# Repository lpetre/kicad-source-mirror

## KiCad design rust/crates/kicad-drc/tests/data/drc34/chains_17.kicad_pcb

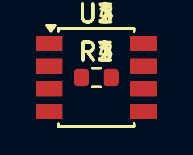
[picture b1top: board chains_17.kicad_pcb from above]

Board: 2 copper layers, 8 parts (0 on the bottom side), 6 nets.

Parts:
R1, R2, R3, R4: R; R_0603_1608Metric
U1, U2, U3, U4: TL071; SSOP-8_3.95x5.21x3.27mm_P1.27mm

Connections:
unnamed: R1.1, U1.6
unnamed: R1.2, R2.1
unnamed: R2.2, U2.6
unnamed: R3.1, U3.6
unnamed: R3.2, R4.1
unnamed: R4.2, U4.6

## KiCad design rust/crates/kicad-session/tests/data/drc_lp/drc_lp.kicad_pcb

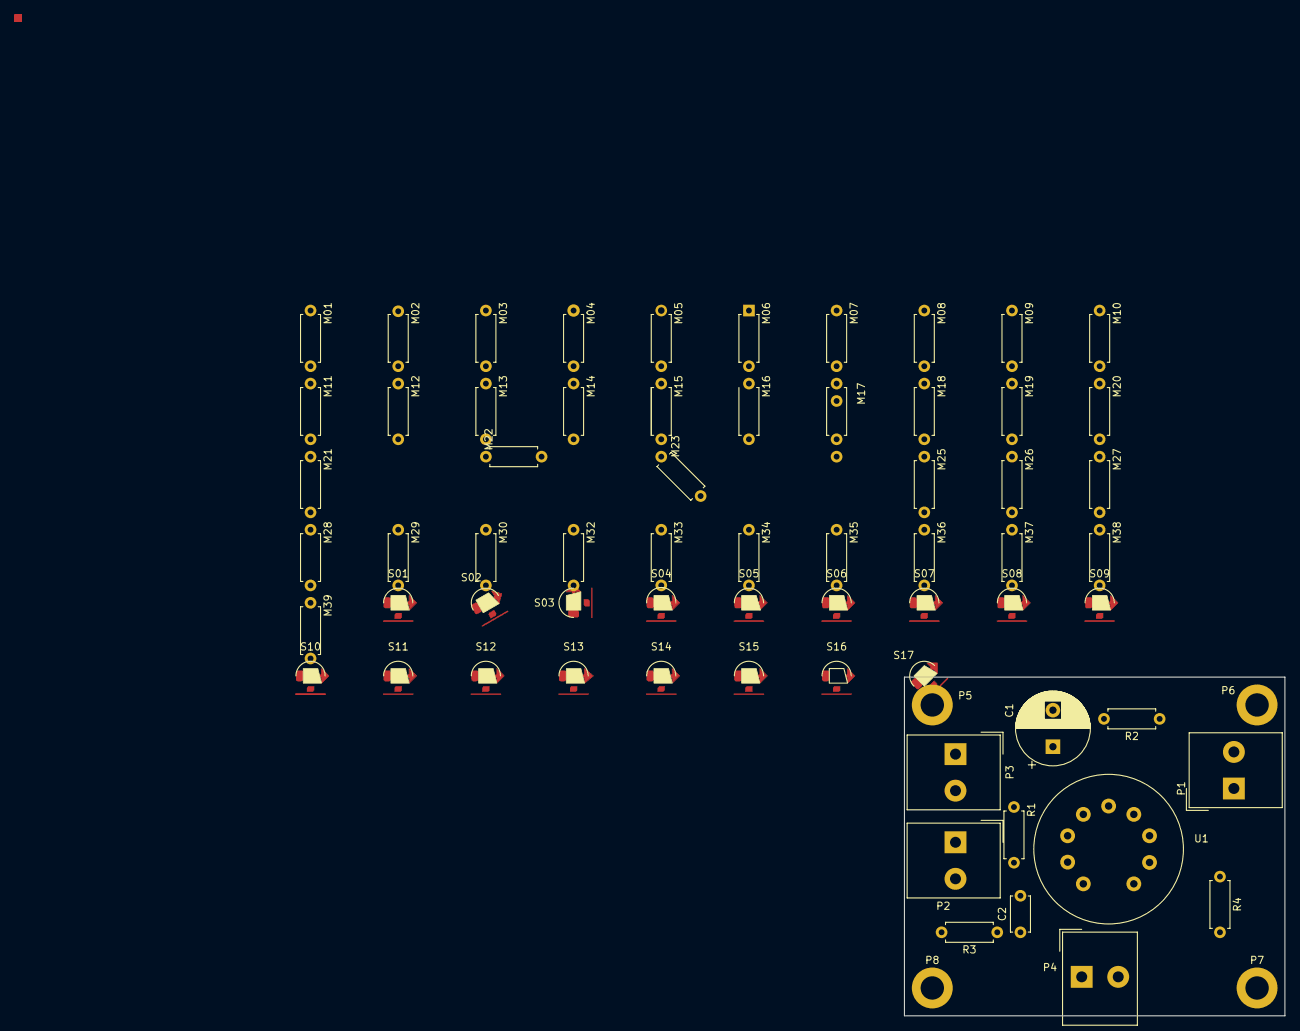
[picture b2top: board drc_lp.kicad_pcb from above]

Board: 2 copper layers, 52.1 x 46.4 mm, 76 parts (1 on the bottom side), 9 nets, no tracks yet.

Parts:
C1: 10uF; CP_Radial_D10.0mm_P5.00mm
C2: 680nF; C_Disc_D4.7mm_W2.5mm_P5.00mm
M01, M02, M03, M04, M05, M06, M07, M08, M09, M10, M11, M12, M13, M14, M15, M16, M17, M18, M19, M20, M21, M22, M23, M24, M25, M26, M27, M28, M29, M32, M33, M34, M35, M36, M37, M38, M39: 1.5K; R_Axial_DIN0207_L6.3mm_D2.5mm_P7.62mm_Horizontal
M30: 1.5K; NoSuchFootprint
P1: IN; Altech_AK300_1x02_P5.00mm_45-Degree
P2: OUT; Altech_AK300_1x02_P5.00mm_45-Degree
P3: POWER; Altech_AK300_1x02_P5.00mm_45-Degree
P4: CONN_2; Altech_AK300_1x02_P5.00mm_45-Degree
P5, P6, P7, P8: MOUNTING_HOLE; MountingHole_3.2mm_M3_DIN965_Pad
R1, R2: 1.5K; R_Axial_DIN0207_L6.3mm_D2.5mm_P7.62mm_Horizontal
R3: 100K; R_Axial_DIN0207_L6.3mm_D2.5mm_P7.62mm_Horizontal
R4: 47K; R_Axial_DIN0207_L6.3mm_D2.5mm_P7.62mm_Horizontal
S01, S02, S03, S04, S05, S06, S07, S08, S09, S10, S11, S12, S13, S14, S15, S16, S17: Shapes
U1: ECC83; Valve_ECC-83-1
Z01, Z02, Z03, Z04, Z05, Z06: ZoneFp

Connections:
GND: C1.2, P1.1, P2.2 (PM), P3.2 (PM), R2.2, R3.2, R4.2
unnamed: P1.2 (PM), R4.1, U1.2 (G)
unnamed: C2.1, P2.1, R3.1
unnamed: C1.1, P3.1, U1.6 (A)
unnamed: P4.1, U1.9 (F2)
unnamed: P4.2 (PM), U1.4 (F1), U1.5 (F1)
unnamed: R1.1, U1.1 (A), U1.7 (G)
unnamed: C2.2, R1.2, U1.8 (K)
unnamed: R2.1, U1.3 (K)
